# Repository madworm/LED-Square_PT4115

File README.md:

LED-Square_PT4115
=================

LAYOUT FILES: 50x50mm LED-Square with PT4115 LED driver.

LED type: Nichia NT2x757DT

---

Before having PC-boards made, please make sure you know about your manufacturer's peculiarities!
Especially drill-sizes and their tolerances may vary too much and give you trouble.

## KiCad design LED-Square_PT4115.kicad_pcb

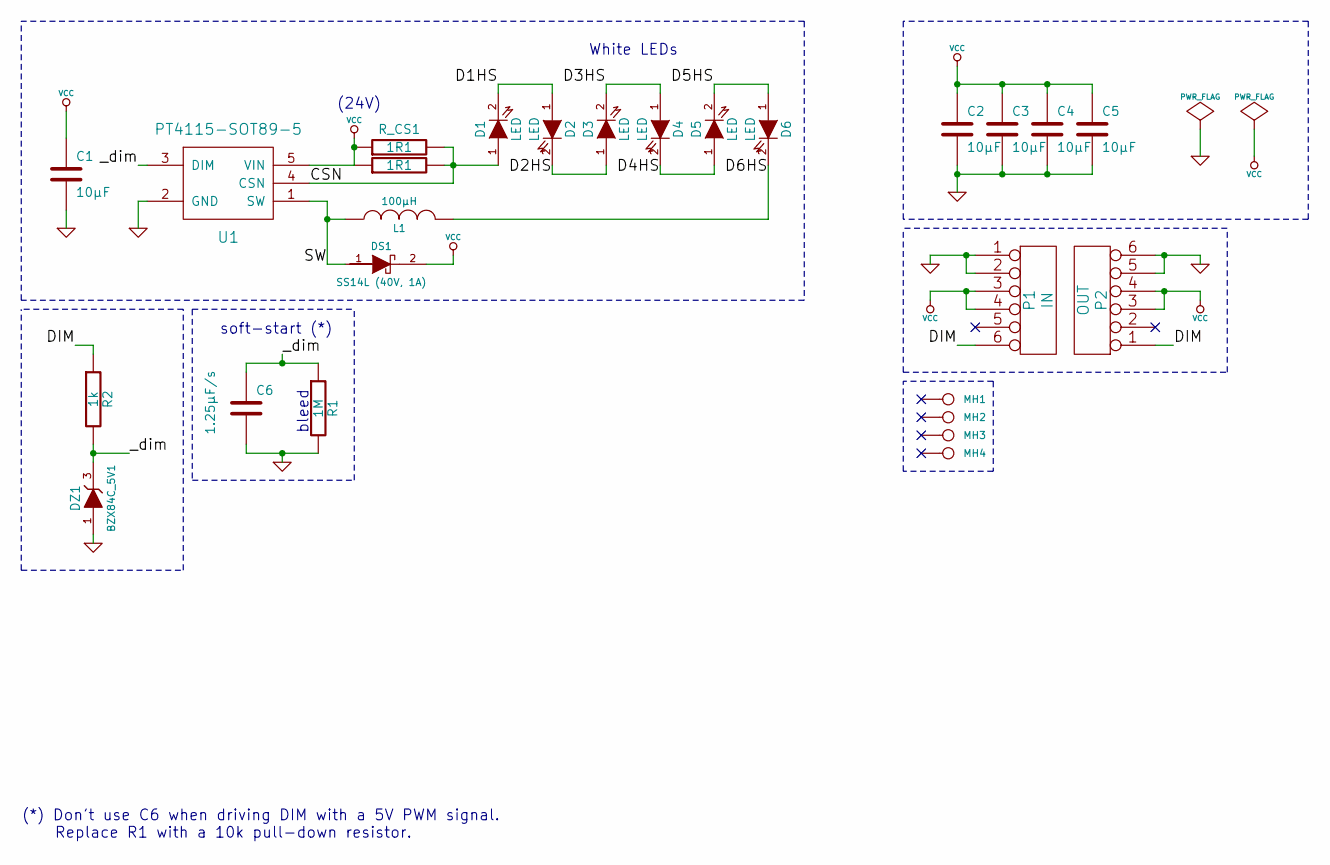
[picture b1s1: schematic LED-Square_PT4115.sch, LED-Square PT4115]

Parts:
C1, C2, C3, C4, C5: 10µF
C6: 1.25µF/s
D1, D2, D3, D4, D5, D6: LED
DS1: SS14L (40V, 1A)
DZ1: BZX84C_5V1
L1: 100µH
MH1, MH2, MH3, MH4: CONN_1
P1: IN
P2: OUT
R1: 1M
R2: 1k
R_CS1, R_CS2: 1R1
U1: PT4115-SOT89-5

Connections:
/CSN: D1.1 (A), R_CS1.2, R_CS2.2, U1.4 (CSN)
/D1HS: D1.2 (K), D2.1 (A)
/D2HS: D2.2 (K), D3.1 (A)
/D3HS: D3.2 (K), D4.1 (A)
/D4HS: D4.2 (K), D5.1 (A)
/D5HS: D5.2 (K), D6.1 (A)
/D6HS: D6.2 (K), L1.2
/DIM: P1.6, P2.1, R2.1
/SW: DS1.1 (A), L1.1, U1.1 (SW)
/_dim: C6.1, DZ1.3, R1.1, R2.2, U1.3 (DIM)
GND: C1.2, C2.2, C3.2, C4.2, C5.2, C6.2, DZ1.1, P1.1, P1.2, P2.5, P2.6, R1.2, U1.2 (GND)
VCC: C1.1, C2.1, C3.1, C4.1, C5.1, DS1.2 (C), P1.3, P1.4, P2.3, P2.4, R_CS1.1, R_CS2.1, U1.5 (VIN)

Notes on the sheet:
bleed
soft-start (*)
(24V)
White LEDs
(*) Don't use C6 when driving DIM with a 5V PWM signal. Replace R1 with a 10k pull-down resistor.

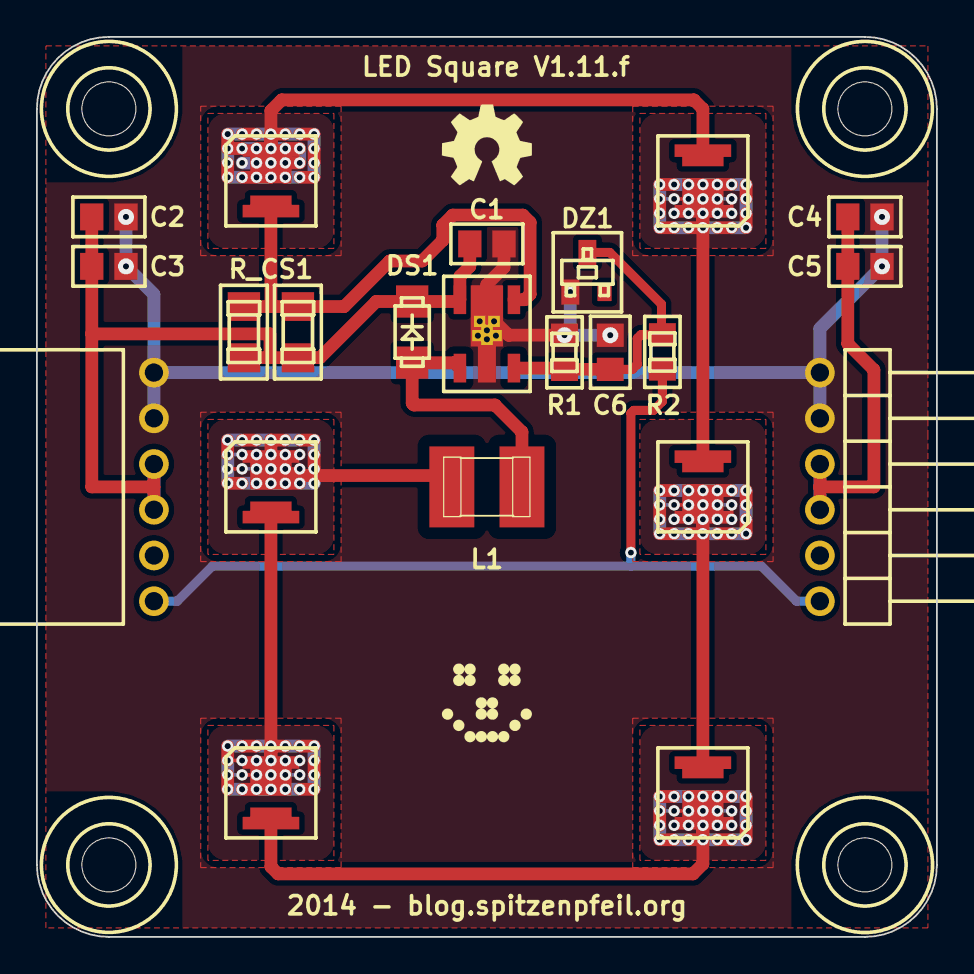
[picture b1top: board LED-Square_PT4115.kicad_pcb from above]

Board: 2 copper layers, 50.0 x 50.0 mm, 28 parts (0 on the bottom side), 12 nets.

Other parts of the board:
G1: OSHW-logo_silkscreen_5mm
G2: LED_smile_silkscreen_5mm

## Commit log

2012-10-05 Added .gitignore file.
2012-10-05 Removed to be ignored files.
2012-10-05 Preparations for the gerber-file stuff.
2012-10-05 Mounting holes might be useful later...
2012-10-05 Had to modifiy the NSS-LED footprint for better hand-soldering...
2012-10-05 Next step: add power connector(s) and maybe a pot for on-board dimming.
2012-10-06 Rounded board edges + 42mm mounting hole spacing ;-)
2012-10-06 Added copper pour as LED heatsinks.
2012-10-16 Created a PNG of the early prototype.
2012-10-22 Added board-to-board connectors.
2012-10-22 Tweaks...
2012-10-23 Added board name + Rev. No. and made a few silkscreen tweaks.
2012-10-23 Changed the inductor footprint pad size to 2.5 x 4.5mm.
    The inductor should be 1812, but it is much wider. More like 1816.
    Not sure if that officially exists...
2012-10-23 Added more copper pour for passive LED cooling + stitching vias.
2012-10-23 Some more copper pour tweaks + shifting vias around.
2012-10-23 Copper pour tweaks.
2012-10-23 Changed the board outline width to 5 mil.
2012-10-23 Moved a trace.
2012-10-24 Added a few more caps on the supply rail.
2012-10-24 Shifted C2-C5 around.
2012-10-24 Increased pad-size of board-to-board connectors.
2012-10-25 Created a PDF for the schematic + gerber files.
2012-10-27 Added soft-start capacitor(s) - optional.
2012-10-29 Last tweaks (I hope).
2012-10-29 Well... some more tweaks.
2012-10-29 Halloween-style silkscreen.
2012-10-29 Small silkscreen tweak.
2012-10-30 Playing with gerbmerge again.
    Still it doesn't translate the silkscreen in the final output...
2012-11-07 Added a logo for KiCad + weblink on the back silkscreen.
2012-11-10 Soft-start: replaced C7 with R1 (1M bleed resistor) for remaining C6.
    R1 is not strictly necessary, but it speeds up discharging C6 a lot.
    Without R1 it takes some time, maybe minutes, until soft-start
    works again.
2012-11-10 Upgraded back silkscreen. VCC 18-24V DC.
2012-11-11 Added a 5.6V Zener to protect the PT4115's DIM input. It badly needs it.
    Upped schematic + pcb revision to V0.2
2012-11-11 Copper pour optimized.
2012-11-12 Rerouted the DIM track.
2012-11-12 Changed the thermal vias of the SOT89-5 package.
    Requires a more recent version of pcbnew to recognize that the GND
    pads overlap and don't need any connecting tracks.
2012-11-12 Tweaks. Started using KiCad Bazaar revision 3752.
2012-11-13 Back silkscreen updated with info regarding PWM and C6 (soft-start).
2012-11-13 Added info regarding PWM-ing DIM and C6 to the schematic.
2012-11-13 Added info to schematic / back silk regarding soft-start vs. ext. PWM.
2012-11-13 Added .txt file with FATAL PT4115 failure modes observed so far.
2012-11-13 Shifted a few vias around.
2012-11-15 Renamed a few gerber-files to match KiCad's new layer names.
2012-11-15 Forgot to adjust gerbv's project files.
2012-11-18 V1.0: Changed LED orientation + rerouted most of the board + new copper pour.
2012-11-18 Small copper pour correction (around mounting holes) + SS tweak.
2012-11-20 Prototype worked well with 1k + 5V1 Zener, so switched to that.
2012-12-12 Renamed some gerbmerge related stuff.
2013-01-02 Played with the copper pour a bit.
2013-01-04 Laser-cut case: first doodles.
2013-01-04 Bidi bidi bidi.
2013-01-04 Dibi dibi dibi.
2013-01-09 Updated make_all-pngs.sh
2013-01-23 Increased drill size for pin-headers to 40mil.
    Did NOT recreate gerber files!
2013-01-23 Recreated the gerber files (40mil drill size issue).
2013-02-22 Changed the thermal copper pour a bit. Didn't recreate gerbers.
2013-02-22 Copper pour + silkscreen tweaks.
2013-06-28 Converted to new kicad board format.
2014-01-14 Fixed silkscreen issues introduced by recent pcbnew 2-line-text-box 'fixes'.
2014-03-05 Fooling around a bit.
2014-03-05 R_CS --> 1206. Couldn't get 1R1 in 0805.
2014-03-05 Tweaks.
2014-03-06 Used B_Cu as heatsink again.
2014-03-06 Heatsink tweaks.
2014-03-06 Silkscreen tweaks.
2014-03-07 More thermal vias for LEDs.
2014-03-19 Added 3D shapes for the board-interconnects.
2014-03-19 Adapted to changed footprint 'MADW__edge-connector_SIL6_female'.
2014-05-27 Updated 'gerber_files/make_all-pngs.sh'.
2014-09-13 Now using 2 pins for the DIM signal as well.
2016-05-03 5.6V Zener --> 5.1V Zener in '...failure-modes.txt'.
